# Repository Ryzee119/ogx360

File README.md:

# ogx360 - Overview

If you like my work please consider a small donation<br>
<br>

The ogx360 is a small circuit board which allows you to use a range of modern USB controllers on the Original Xbox Console.

* A simple video showing some its feature is on youtube https://youtu.be/ycZjQUjz1Fk
* Another video attempting to show the input lag is here: https://youtu.be/V7Pnba7Y12Y
* Another video showing the Steel Battalion Controller support is here: https://youtu.be/g_eQlOcccg8

## Features include:
* Full rumble support on all controllers.
* Steel Battalion controller support with an Xbox 360 Chatpad using Xbox 360 Wireless Controllers.
* Low level programming with minimal input lag. Less than 4ms over an original controller. (See https://youtu.be/V7Pnba7Y12Y)
* Firmware can be updated over USB. No programming hardware is required. See [Firmware](./Firmware).
* One ogx360 mutliple Xboxes, just plug the other Arduino modules into nearby OG Xbox consoles.
* Flip the axis on the right stick for those games missing axis inversion settings. (Hold the right stick in then D-PAD to invert that direction).

## Supported controllers
* Supports 4 players with Genuine and Third Party Microsoft Xbox 360 Wireless Receivers.
* Wired Xbox 360 Controllers.
* 8bitdo Wireless Bluetooth Adaptor (See http://www.8bitdo.com/wireless-usb-adapter/ for supported controllers). One controller per 8bitdo adaptor.
* ChronusMAX/ChronusZen (See https://cronusmax.com/ for supported devices). Ensure it is configured to appear as an Xbox 360 Controller. One controller per adaptor.
* Most/all? controllers that are xinput compatible.
* Genuine and PDP Wired Xbox One Controllers.
* Hyperkin Duke Xbox One Controller.
* **NOTE** - When connecting multiple USB bus powered devices, a USB2.0 hub is required. A externally powered hub is recommended.

## Steel Battalion controller emulation
* You need a wireless Xbox 360 controller with a chatpad peripheral.
* You can change what the controller appears to the console at anytime, so you can use the 'Duke Controller' to boot into the game, then change to the 'Steel Battalion controller' whilst in game. 
* Button mapping is below. (High Res image available [here](https://i.imgur.com/12SawzC.png)).

## Connection to your Xbox

By Ryzee119

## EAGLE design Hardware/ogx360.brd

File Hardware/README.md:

# ogx360 - Hardware
This folder contains the schematic and PCB layout files and the PCB Gerber files. These were created using [Autodesk Eagle.](https://www.autodesk.com/products/eagle/overview)

* The PCB Gerbers and BOM are located [here](../.kitspace/).
* These can easily be ordered via [kitspace](https://kitspace.org/boards/github.com/ryzee119/ogx360).
  * Note: you may wish to order extra of the small components (resistors, capacitors, etc.) as it is easy to loose some when hand-soldering.
* 3D model of the PCB is [here](https://a360.co/3aavAXA) (Fusion360).
* Note: On the corner of the Arduino modules there is a solder jumper labelled J1. It is recommended you bridge this with a solder blob.

## Some other needed items
| Qty | Value/Model | Link|
| --- | --- | --- |
| Up to 4 | ARDUINO_LEONARDO_MICRO 5V/16Mhz | [Any clones](https://www.aliexpress.com/item/New-Pro-Micro-for-arduino-ATmega32U4-5V-16MHz-Module-with-2-row-pin-header-For-Leonardo/32768308647.html). Only one is compulsory. 2,3 and 4 will add support for Player 2,3, 4 respectively. Make sure you get the 5V/16Mhz variant. |
| Up to 4 | Xbox Controller Port to MicroUSB cable | [ChimericSystems](https://www.chimericsystems.com/product/micro-usb-to-xbox-cable/) or [Alibaba (Large MOQ!)](https://www.alibaba.com/product-detail/for-XBOX-MicroUSB-Cable-for-Xbox_62222784495.html) or DIY |

## Cases
If you make a case or something similar I can put it here if you're happy to share!
* By bluemeanie23 at [Tinkercad](https://www.tinkercad.com/things/kJb02GCUetG).
* By culexus at [Thingiverse](https://www.thingiverse.com/thing:3510779?fbclid=IwAR1Hd3BBLBxFbMWYJ0MO9VCzgxWrqV2Efiftj0Rz7HYnv9ODGwWncQdSh4I).

## Schematic

By Ryzee119

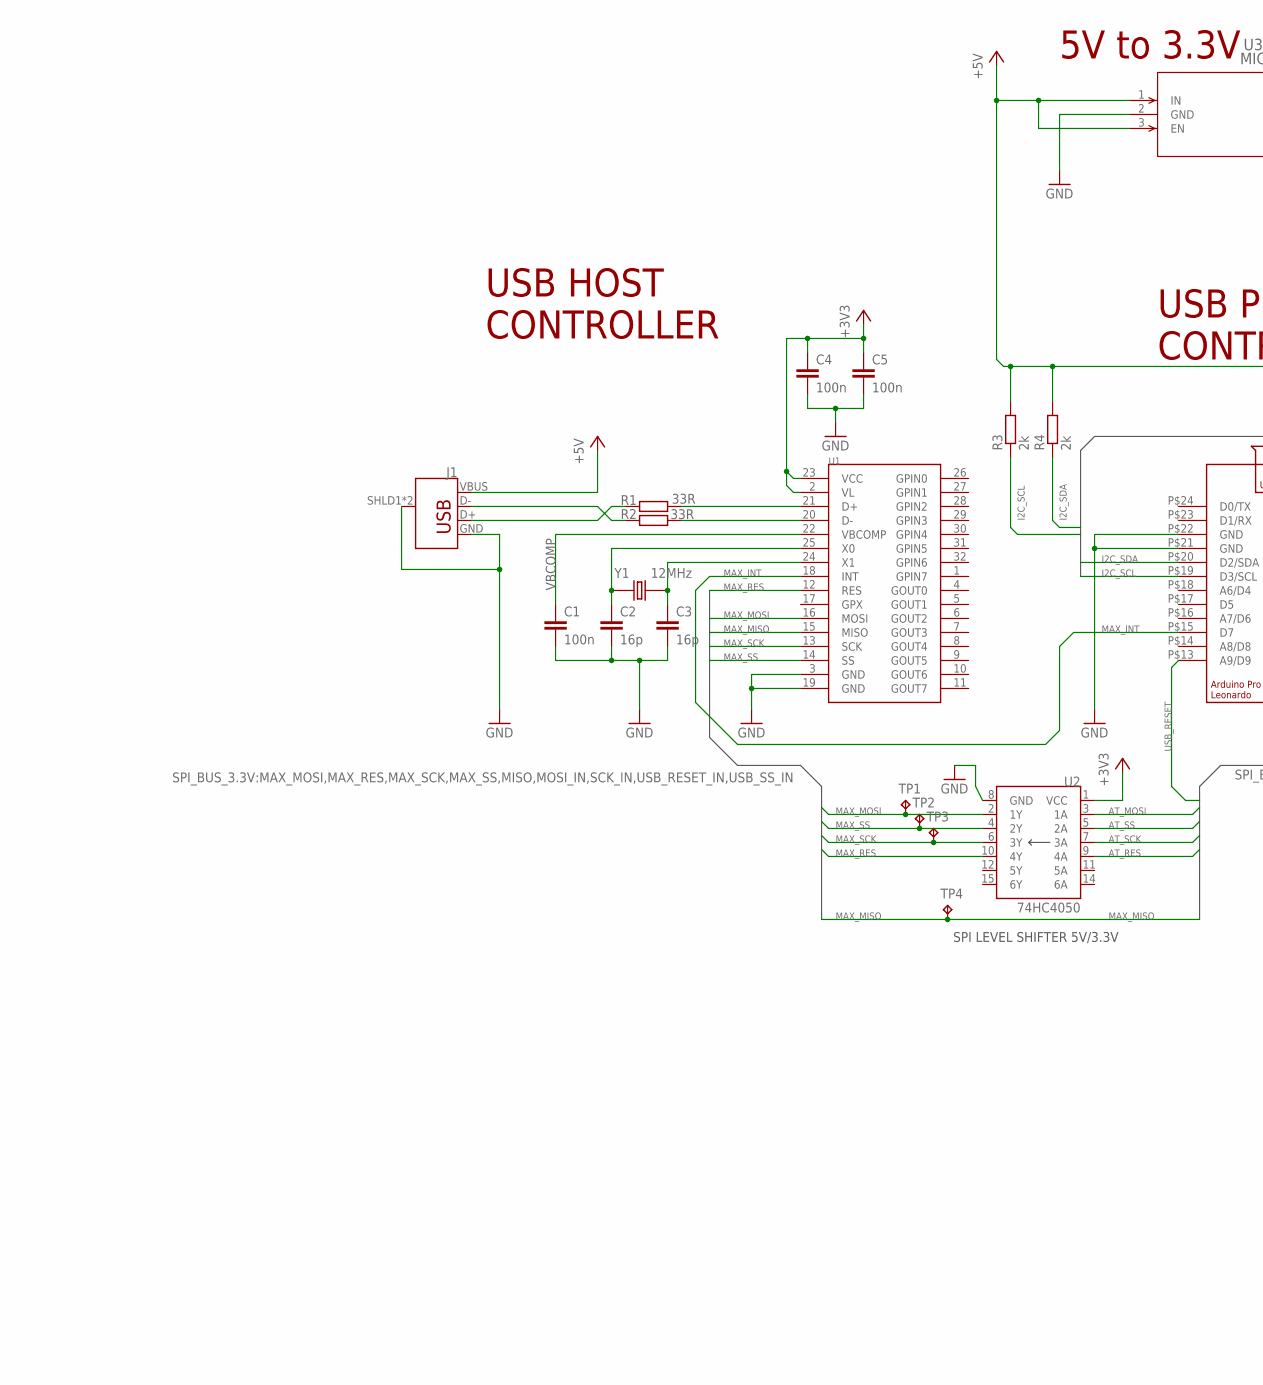
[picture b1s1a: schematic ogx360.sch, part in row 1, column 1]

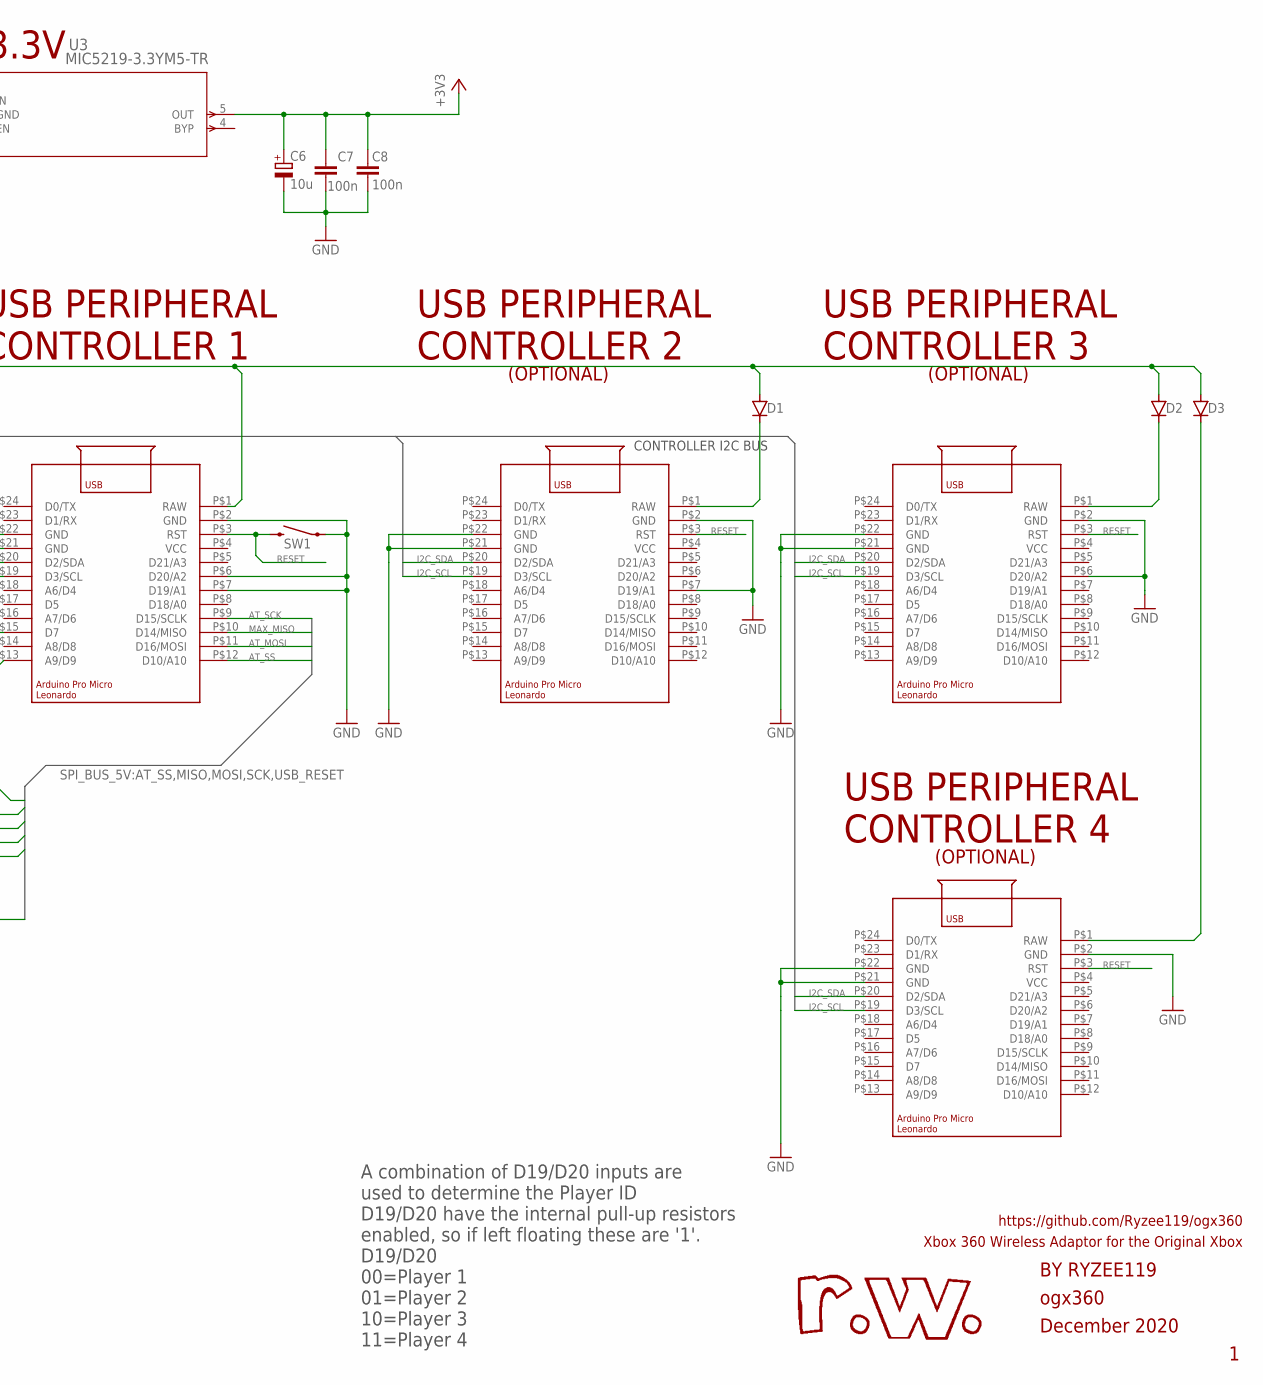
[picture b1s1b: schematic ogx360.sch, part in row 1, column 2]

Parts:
C1, C4, C5, C7, C8: 100n; C0805
C2, C3: 16p; C0805
C6: 10u; 153CLV-0405
D1, D2, D3: DIODE-SOD123; SOD123
J1: USB_A_SMT_FEMALE_NS; USB-A-S-NOSILK-FEMALE
R1, R2: 33R; R0805
R3, R4: 2k; R0805
SW1: TL3305AF160QG
TP1, TP2, TP3, TP4: TPTP10R; TP10R
U1: MAX3421ETQFP32-5MM; TQFP32-5X5MM
U2: 74HC4050; SO16
U3: MIC5219-3.3YM5-TR; SOT-23-5_M5_MCH
U4, U5, U6, U7: ARDUINO_LEONARDO_MICRO
Y1: 12MHz; XTAL_ECS-250-18-5PX-JEM-TR

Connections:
+3V3: C4.1, C5.1, C6.+, C7.1, C8.1, U1.2 (VL), U1.23 (VCC), U2.1 (VCC), U3.5 (OUT)
+5V: D1.A, D2.A, D3.A, J1.VBUS, R3.2, R4.2, U3.1 (IN), U3.3 (EN), U4.P$1 (RAW)
+5V_SLAVE1: D1.C, U5.P$1 (RAW)
+5V_SLAVE2: D2.C, U6.P$1 (RAW)
+5V_SLAVE3: D3.C, U7.P$1 (RAW)
AT_MOSI: U2.3 (1A), U4.P$11 (D16/MOSI)
AT_RES: U2.9 (4A)
AT_SCK: U2.7 (3A), U4.P$9 (D15/SCLK)
AT_SS: U2.5 (2A), U4.P$12 (D10/A10)
D_N: R2.1, U1.20 (D-)
D_P: R1.1, U1.21 (D+)
GND: C1.2, C2.2, C3.2, C4.2, C5.2, C6.-, C7.2, C8.2, J1.GND, J1.SHLD1 (SHIELD), J1.SHLD2 (SHIELD), SW1.P$3 (2), SW1.P$4 (2), U1.3 (GND), U1.19 (GND), U2.8 (GND), U3.2 (GND), U4.P$2 (GND), U4.P$6 (D20/A2), U4.P$7 (D19/A1), U4.P$21 (GND), U4.P$22 (GND), U5.P$2 (GND), U5.P$7 (D19/A1), U5.P$21 (GND), U5.P$22 (GND), U6.P$2 (GND), U6.P$6 (D20/A2), U6.P$21 (GND), U6.P$22 (GND), U7.P$2 (GND), U7.P$21 (GND), U7.P$22 (GND)
I2C_SCL: R3.1, U4.P$19 (D3/SCL), U5.P$19 (D3/SCL), U6.P$19 (D3/SCL), U7.P$19 (D3/SCL)
I2C_SDA: R4.1, U4.P$20 (D2/SDA), U5.P$20 (D2/SDA), U6.P$20 (D2/SDA), U7.P$20 (D2/SDA)
MAX_INT: U1.18 (INT), U4.P$15 (D7)
MAX_MISO: TP4.TP, U1.15 (MISO), U4.P$10 (D14/MISO)
MAX_MOSI: TP1.TP, U1.16 (MOSI), U2.2 (1Y)
MAX_RES: U1.12 (RES), U2.10 (4Y)
MAX_SCK: TP3.TP, U1.13 (SCK), U2.6 (3Y)
MAX_SS: TP2.TP, U1.14 (SS), U2.4 (2Y)
unnamed: J1.D+, R1.2
unnamed: J1.D-, R2.2
unnamed: C2.1, U1.25 (X0), Y1.1
unnamed: C3.1, U1.24 (X1), Y1.2
RESET: SW1.P$1, SW1.P$2, U4.P$3 (RST), U5.P$3 (RST), U6.P$3 (RST), U7.P$3 (RST)
USB_RESET: U4.P$13 (A9/D9)
VBCOMP: C1.1, U1.22 (VBCOMP)

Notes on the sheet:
USB HOST CONTROLLER
ogx360
December 2020
BY RYZEE119
Xbox 360 Wireless Adaptor for the Original Xbox
https://github.com/Ryzee119/ogx360
USB PERIPHERAL CONTROLLER 1
USB PERIPHERAL CONTROLLER 2
5V to 3.3V
A combination of D19/D20 inputs are used to determine the Player ID D19/D20 have the internal pull-up resistors enabled, so if left floating these are '1'. D19/D20 00=Player 1 01=Player 2 10=Player 3 11=Player 4
USB PERIPHERAL CONTROLLER 3
USB PERIPHERAL CONTROLLER 4
(OPTIONAL)
CONTROLLER I2C BUS
SPI LEVEL SHIFTER 5V/3.3V

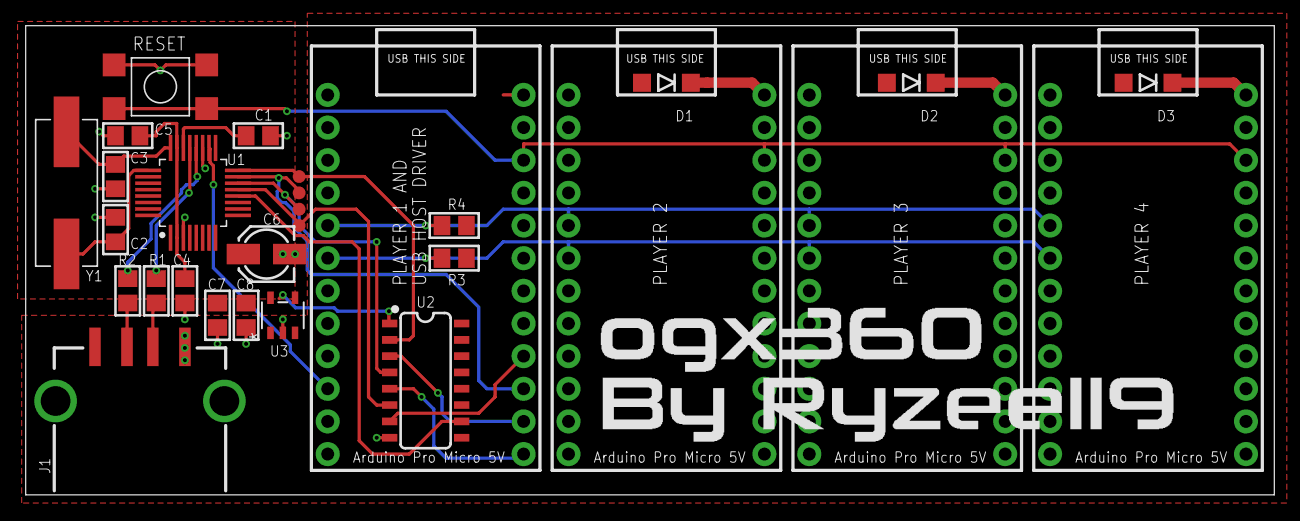
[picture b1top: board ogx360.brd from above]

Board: 2 copper layers, 97.1 x 36.5 mm, 29 parts (0 on the bottom side), 25 nets.

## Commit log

2018-12-15 Formatting
2018-12-15 Update README.md
    spelling
2018-12-22 Optimizations and cleanup
2019-01-06 Fixed rare rumble bug and soft reset bug
2019-01-21 General optimizations, experimental build added
2019-01-23 Minor fixes
2019-01-27 Swapped black and white buttons
2019-01-28 Added Arduino clone ref
2019-02-02 Add self-test script
2019-02-02 Add self test script
2019-02-02 Fixed link
2019-02-25 Added SB Controller Support
2019-02-25 Typos
2019-03-11 Added Rumble Feedback to SB, Tweaked SB Button Mapping, bug Fixes, Optimizations. SB Protocol Notes
2019-03-16 stocked
2019-03-21 Added Cases and other minor text changes
2019-03-22 Added another case
2019-04-09 8bitdo adaptor support, tweak SB controller mapping, added SB ssensitivity adjust, Wired 360 in main firmware now
2019-05-29 Fixed issue#2
2019-06-20 Added PID 0x2AA for a new wireless receiver found by users
2019-07-04 Fixed rumble pipe for 8btido controllers, gitinore and editorconfig added, formatting etc.
2019-08-02 Updated part for LED. Refer Issue #9
2019-08-24 Code clean up, fixed some back end stuff. Xbox 360 wireless init sequence closer to genuine, polls slaves on power up to confirm they're presetn
2019-08-28 Fixed issue #12, Fixed THPS 2X rumble issue, Fixed XblastOS hotplug issue
2019-08-28 Moved compiled binaries to releases
2019-09-21 Added PID 0x02A9
2019-10-24 added VID=0x0738 PID=0x4738
2019-11-15 Fix controller documentation link
    Looks like the link on xboxdevwiki.net was changed.
2020-03-15 Added hyperkin duke, alot of code refactoring, fixed bug in xbox one driver
2020-05-24 Update and fix GameStop and Afterglow wired controllers VID/PID values.
2020-05-24 Keep gamestop and afterglow PIDs and add new ones to keep compatibility.
2020-05-26 Added madcatz wired controller vid/pid, thrustmaster wired controller vid/pid and thrustmaster wheel vid/pid. All three tested and working.
2020-06-07 Added support for: - Street Figter 4 Fight Pad (Xbox 360) - Hori Rap VX-SA Arcade Stick (Xbox 360)
2020-07-02 Add MADCATZ_BEAT_PAD and KONAMI_DANCE_PAD
2020-07-03 Remove redundant VIDs
2020-07-03 USBD: Add MADCATZ_BEAT_PAD and KONAMI_DANCE_PAD
2020-07-04 GH: Update gitignore
2020-07-04 Refactor Xbox
2020-08-21 README: Simplify
2020-08-21 Allow defines to be passed via make
2020-08-22 Working CMake config for master and slave builds
2020-08-22 Added GitHub Actions CI Workflow to auto-build
2020-08-23 Removed extra lib files from main firmware files
    Originally I was building the libs as part of the main build, but then I split them out into separate libraries. I forgot to remove some of the library files from the main firmware files list, so it 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
2020-08-23 Upload build artifacts when pushing to master
2020-08-23 Fixed comment spacing in XBOXRECV.h
2020-08-23 Split CMAKE compile flags to multiple lines
2020-08-23 Add build status badge
2020-09-27 ci: correctly creates hex from elf
2020-09-28 XBOXONE: Add Hyperkin Duke v1.01
2020-10-08 Increase delay around reset to fix stability issues during boot with 3rd party XBox 360 Wireless Receiver.
2020-10-08 Fix comment.
2020-11-25 Input: Dont clear buttons until report is send
2020-12-05 XBOXRECV: Rework to reduce missed presses with chatpad
2020-12-05 XBOXRECV: Fix incorrect chatpad button states
2020-12-05 XBOXRECV: Reformat code
2020-12-05 XBOXRECV: Refresh LED periodically
2020-12-07 XBOXRECV: Check controller presence only when idle
2020-12-07 XBOXRECV: Reformat header
2020-12-07 PlatformIO: Migrate build system
2020-12-07 USBD: Reformat code
2020-12-07 Main: Reformat code
2020-12-07 PlatformIO: Update CI
2020-12-07 PlatformIO: Update build instructions
2020-12-07 PlatformIO: Setup build environments
2020-12-08 XBOXRECV: Correctly limit out pipe to 8ms
2020-12-08 XBOXRECV: Reset idle only on controller press
2020-12-08 Main: Fix order of USBTask. Slight improvment in input lag
2020-12-08 XBOXRECV: Add timeouts and enumerate based on interface
2020-12-08 XBOXRECV: Out pipe timer should be static
2020-12-08 XBOXUSB: Reformat code
2020-12-08 XBOXUSB: Reformat header
2020-12-08 XBOXUSB: Improve output command reliability
2020-12-08 XBOXRECV: Check if no input before clearing buffer
2020-12-08 XBOXRECV: Increase Keep Alive Packet Frequency
2020-12-13 XBOXUSB Add support to v1.14 wired controller & minor bug fix
2020-12-26 Rumble fix for Steel Battalion
2021-01-09 HW: PCB to revision 1
2021-01-09 HW: Migrate to kitspace
2021-01-09 HW: Move cases to Hardware readme
2021-01-09 FW: Link the xboxdevwiki
2021-01-09 README: Simplify text
2021-01-09 GH: Remove editorconfig
2021-01-09 BOM: Remove Arduino link
2021-01-09 BOM: Fix unknown characters
2021-01-09 README: Add paypal link
2021-01-09 HW: Route reset trace
2021-01-09 XBOXUSB: Properly parse config descriptor
2021-01-09 Images: Add revised PCB photo
2021-01-09 README: Update image to latest PCB
2021-01-09 HW: Update schematic image
2021-01-09 Images: Delete unused images
2021-01-09 README: Fix image link for self test
2021-01-09 Main: Add ability to invert right stick Y-axis
2021-01-10 Readme: Missing a word
2021-02-12 XBOXONE: Format code
2021-02-12 XBOXONE: Add Xbox S/X PID 0x0B12 support
2021-02-12 CI: Create artifact
2021-02-15 Input: Allow inverstion of X and Y axis on right stick.
2021-03-06 XBOX360: Add RF module support
2021-05-06 PlatformIO: Build with -fdata-sections
2021-06-04 USBD: Remove LUFA
2021-06-04 Core: Add ArduinoCore as a submodule
2021-06-04 USBH: Add UHS2 as submodule
2021-06-04 USBH: Remove legacy UHS
2021-06-04 USBD: Add initial XID pluggable USB driver
2021-06-04 USBD: Remove legacy LUFA XID drivers
2021-06-04 USBD: Rename XID driver
2021-06-04 USBD: Move device driver to folder
2021-06-04 USBH: Add initial XINPUT driver
2021-06-04 USBH: Update licensing
2021-06-04 USBD: Update licensing
2021-06-05 USBH: Driver additions
2021-06-05 Main: start master handler
2021-06-05 Build: Update for v2 structure
2021-06-06 Build: disable UHS debugging
2021-06-06 USBD: Driver cleanup
2021-06-06 Main: Update for v2
2021-06-06 Master: Update for v2
2021-06-06 Build: Recursive checkout
2021-06-06 Master: add slave communications
2021-06-06 USBD: Add steelbattalion fixme
2021-06-06 Disable usb interface if disconnected
2021-06-06 USBH: Use single buffer
2021-06-06 USBH: Remove unused buffer
2021-06-06 USBH: Fix missing bracket
2021-06-06 XINPUT: Enumeration cleanup
2021-06-06 XINPUT: Cleanup header
2021-06-07 XINPUT: Dont spam output pipes
2021-06-07 XINPUT: Add chatpad_keepalive_toggle
2021-06-07 XINPUT: Fix chatpad keepalive toggle
2021-06-07 XINPUT: Clean up polling
2021-06-07 XINPUT: Should actually return NULL on Poll
2021-06-07 XINPUT: Simplify LED and Rumble commands
2021-06-07 XINPUT: Simplify Rumble and LED commands
2021-06-07 XINPUT: Use global buffer
2021-06-07 XINPUTS: Oops
2021-06-07 Build: Single file build
2021-06-07 XINPUT: Fix string printing
2021-06-07 XINPUT: Fix out timer and cleaner chatpad led
2021-06-08 XINPUT: driver updates
2021-06-08 Build: Define UHS serial
2021-06-08 XINPUT: Power off if holding xbox button
2021-06-08 USBD: Fix out pipe reading, formatting
2021-06-08 USBD: WIP
2021-06-08 USBH: WIP
2021-06-08 Main: WIP
2021-06-09 Main: cleanup
2021-06-09 merge
2021-06-09 loop count
2021-06-12 USBH: Add UHS2 as a submodule
2021-06-12 USBD: Remove legacy usbd driver
2021-06-12 USBD: Add PluggableUSB XID driver
2021-06-12 Master: Add master handler
2021-06-12 Slave: Add slave handler
2021-06-12 Main: Update main for v2
2021-06-12 Build: Update build config for v2
2021-06-12 FW: Update readme for v2
2021-06-12 HW: Add note about J1
2021-06-12 Input: Allow inversion of RS x and y axis
2021-06-12 Build: Clone recursively to get submodules
2021-06-15 XINPUT: Rework enumeration
2021-06-17 XID: Fix rumble locking on
2021-06-17 XINPUT: Get product string on enumeration
2021-06-17 XINPUT: Add pointer to optional user data struct
2021-06-18 Input: Rework Steel Battalion
2021-06-18 Main: Handle more USB Hubs
2021-06-19 Input: Allow adjusted SB sensitivity
2021-06-19 Input: Remove gear lever init from main
2021-06-22 UH2: Update submodule
2021-06-30 Build: Allow re-running build
2021-07-05 Readme: Update for v2
2021-07-07 HW: Update license
2021-10-01 fix enum typo
2021-10-02 USBD: Fix enum typo
2022-01-15 Core : Update submodule to 505b4ca
2022-01-15 UHS2: Update submodule
2022-01-15 XINPUT: Start with one valid ep on init
2022-01-15 XINPUT: Correctly handle devices with multiple interfaces
2022-01-15 Main: Make LEDs behave like legacy firmware
2022-01-15 XINPUT: Update for new USB Core backend
2022-01-15 USBH: Manually probe USB bus too
2022-01-15 USBH: Update submodule URL
2022-01-15 XINPUT: Add mouse/keyboard supoort
2022-01-15 XINPUT: Handle 8bitdo wireless adaptor 2
2022-05-30 xinput: Add PowerA init packets
2022-05-30 xinput: Add init packets for PowerA branded xbone controllers
2022-06-06 pio: Replace depreciated src_filter
2022-06-06 xinput: Only grab first interface from xbone controllers
2023-04-07 Make component quantities in BOM correct
    Fixes https://github.com/Ryzee119/ogx360/issues/106
2023-04-07 Add note about ordering extra small components
2025-04-01 usbd: Only send what is requested in setup packet
2025-04-01 ci: Bring up
2025-04-01 README: Fix CI Badge

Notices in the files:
parts and their libraries:
SparkFun-IC-Comms: Licensing: Creative Commons ShareAlike 4.0 International - https://creativecommons.org/licenses/by-sa/4.0
COPYRIGHT: Copyright (C) 2018 Accelerated Designs. All rights reserved
